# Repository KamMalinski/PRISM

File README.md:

# PRISM

**PCB Recognition and Intelligent Schematic Mapping**

PRISM reconstructs an editable KiCad schematic from aligned images of the top
and bottom sides of a PCB. It combines image processing, pad and trace
detection, OCR-assisted component recognition, connectivity analysis, manual
correction tools, and schematic optimization in one desktop application.

> PRISM is currently alpha software. Generated connectivity and component
> assignments must be reviewed before they are used for manufacturing,
> servicing, or safety-critical work.

## Features

- guided import of TOP and BOTTOM PCB images;
- automatic or manually sampled solder-mask and copper colors;
- board alignment, pad pairing, trace detection, and net reconstruction;
- OCR-assisted labels and component candidates;
- interactive correction editor for pads, traces, pairs, OCR, and components;
- text netlist and KiCad schematic export;
- optional KiCad CLI validation and schematic optimization;
- native desktop builds for Windows, macOS, and Linux.

## Requirements

- Python 3.11 or newer when running from source;
- Tk 8.6 or newer;
- Tesseract OCR for OCR features;
- KiCad with `kicad-cli` for round-trip validation and optimized previews.

PRISM searches `PATH` first and then conventional installation locations for
the current operating system. Tesseract can also be selected manually in the
interface.

On Debian or Ubuntu, install the native GUI and OpenCV runtime libraries before
running from source or building:

```bash
sudo apt-get install python3-venv python3-tk libgl1 libglib2.0-0
```

## Run From Source

Create and activate a virtual environment, then install the project:

```bash
python -m venv .venv
```

Windows PowerShell:

```powershell
.\.venv\Scripts\Activate.ps1
python -m pip install -r requirements.txt
prism
```

macOS and Linux:

```bash
source .venv/bin/activate
python -m pip install -r requirements.txt
prism
```

Windows users can alternatively run `.\run.ps1`.

## Build Native Packages

PyInstaller creates native applications and does not cross-compile. Run the
matching script on each target operating system:

```powershell
# Windows
.\scripts\build\build_windows.ps1
```

```bash
# macOS
bash scripts/build/build_macos.sh

# Linux
bash scripts/build/build_linux.sh
```

The scripts create an isolated `.venv-build` environment and use the shared
configuration in `scripts/build/package.py`.

| Platform | Output |
| --- | --- |
| Windows | `dist/PRISM/PRISM.exe` |
| macOS | `dist/PRISM.app` |
| Linux | `dist/PRISM/PRISM` |

Windows and Linux use PyInstaller's `onedir` layout. Distribute the complete
`dist/PRISM` directory, not only the executable. The macOS application is
unsigned; public releases should be code-signed and notarized by the release
owner.

## Basic Workflow

1. Select images of the top and bottom PCB sides.
2. Confirm automatic color detection or collect color samples manually.
3. Run the analysis.
4. Review detected geometry and connectivity in the correction editor.
5. Recalculate after corrections and inspect the generated netlist.
6. Open the result directory and validate the KiCad schematic.

Generated files are written under `~/PRISM/results` by default. Set the
`PRISM_OUTPUT_DIR` environment variable to use a different location. A local
`results/` directory is also excluded from version control.

## Dataset

[`Dataset/`](Dataset/README.md) contains twelve PCB examples with TOP/BOTTOM
images and reference KiCad projects. It is intended for repeatable development
and evaluation, not as a formal train/test split.

## Project Structure

```text
.
|-- Dataset/                         Test images and reference KiCad projects
|-- scripts/build/                   Native build entry points and shared build logic
|-- src/schematic_generator/
|   |-- assets/                      Application and executable icons
|   |-- correction_editor/           Manual reconstruction editor
|   |-- detection/                   Pad, trace, plane, and pair detection
|   |-- diagnostics/                 Diagnostic reports
|   |-- geometry/                    Alignment and rectification
|   |-- gui/                         Main desktop workflow
|   |-- kicad/                       KiCad serialization and routing
|   |-- netlist/                     Connectivity and component inference
|   |-- schematic/                   Validation and optimization
|   |-- platform_support.py          Operating-system integration
|   `-- __main__.py                  Application entry point
|-- pyproject.toml                  Package metadata and runtime dependencies
|-- requirements-build.txt          Build-only dependencies
`-- requirements.txt                Editable development installation
```

## Automated Builds

The GitHub Actions workflow in `.github/workflows/build.yml` runs smoke tests
and creates Windows, macOS, and Linux artifacts using the same scripts as local
builds.

## Contributing

Keep platform-independent behavior in the application modules. Operating-system
differences belong in `platform_support.py`, while packaging differences belong
in `scripts/build/package.py`. New detection or reconstruction behavior should
be checked against multiple samples from `Dataset/`.

## License

No project license has been selected yet. Add a `LICENSE` file before presenting
PRISM as open-source software or accepting external contributions.

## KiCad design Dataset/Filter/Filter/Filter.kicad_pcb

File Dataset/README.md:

# PCB Test Dataset

This directory contains a curated test dataset of small PCB examples used for
evaluating PCB image analysis and schematic reconstruction workflows.

Each sample contains:

- two raster images of the PCB, one for the top side and one for the bottom
  side;
- a KiCad project directory with the reference PCB and schematic files.

## Directory Structure

The dataset is organized by sample name:

```text
Dataset/
  Cascade/
    TOP.png
    BOTTOM.png
    Cascade/
      Cascade.kicad_pcb
      Cascade.kicad_sch
      Cascade.kicad_pro
      Cascade.kicad_prl
  Connector/
    TOP.png
    BOTTOM.png
    Connector/
      Connector.kicad_pcb
      Connector.kicad_sch
      Connector.kicad_pro
      Connector.kicad_prl
  ...
```

## Samples

| Sample | Purpose / PCB feature represented | Top image | Bottom image | KiCad project folder |
| --- | --- | --- | --- | --- |
| `Cascade` | Cascaded circuit blocks and multi-stage connectivity | `TOP.png` | `BOTTOM.png` | `Cascade/` |
| `Connector` | Connector-style topology and external pin grouping | `TOP.png` | `BOTTOM.png` | `Connector/` |
| `Crossover` | Crossing or overlapping routing patterns between nets | `TOP.png` | `BOTTOM.png` | `Crossover/` |
| `Divider` | Simple divider-like circuit topology | `TOP.png` | `BOTTOM.png` | `Divider/` |
| `Elements` | Board with a larger number of components/elements | `TOP.png` | `BOTTOM.png` | `Elements/` |
| `Filter` | Filter-like circuit topology | `TOP.png` | `BOTTOM.png` | `Filter/` |
| `Floating` | Floating or weakly connected structures | `TOP.png` | `BOTTOM.png` | `Floating/` |
| `Groundplane` | Board containing a large copper groundplane/fill area | `TOP.png` | `BOTTOM.png` | `Groundplane/` |
| `Meander` | Meandered routing geometry | `TOP.png` | `BOTTOM.png` | `Meander/` |
| `Round` | Rounded or curved routing geometry | `TOP.png` | `BOTTOM.png` | `Round/` |
| `Simple` | Simple baseline board | `TOP.png` | `BOTTOM.png` | `Simple/` |
| `Transistors` | Board containing transistor-based circuitry | `TOP.png` | `BOTTOM.png` | `Transistors/` |

## File Formats

The raster images are PNG files. They should be interpreted as pixel images of
the PCB sides:

- `TOP.png` - top side image;
- `BOTTOM.png` - bottom side image.

The KiCad project directories contain:

- `*.kicad_pcb` - reference PCB layout;
- `*.kicad_sch` - reference schematic;
- `*.kicad_pro` - KiCad project metadata;
- `*.kicad_prl` - KiCad project local/session settings.

The KiCad files are intended as reference design files for validating generated
schematics, connectivity, component placement, and PCB reconstruction results.

## How to Interpret the Data

The PNG images are the primary inputs for image-processing and reconstruction
algorithms. The corresponding KiCad files are the reference data for the same
sample.

When using the dataset:

1. Treat each top-level directory as one independent PCB test case.
2. Load the top and bottom PNG images as the two observed PCB sides.
3. Use the KiCad files in the nested project directory as reference design
   data.
4. Compare generated outputs against the reference schematic or PCB project,
   depending on the evaluated task.

The dataset does not define a train/test split. If a split is needed, define it
explicitly in the experiment protocol.

## Expected Use

This dataset is suitable for:

- testing PCB side alignment;
- detecting pads, traces, holes, copper pours, and component-like structures;
- reconstructing netlists from PCB images;
- generating or validating KiCad schematic files;
- comparing algorithm behavior on boards with different routing patterns.

## Notes

- Raster image units are pixels.
- KiCad coordinate data should be interpreted according to KiCad file format
  conventions, typically in millimeters for design coordinates.
- The dataset contains PCB design examples and does not contain personal or
  human-subject data.

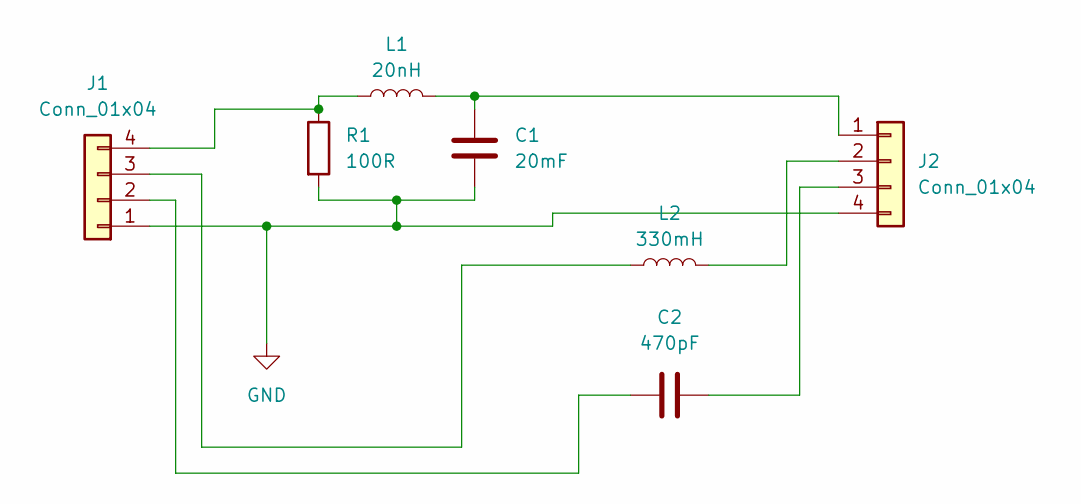
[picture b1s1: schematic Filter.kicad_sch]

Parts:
C1: 20mF; CP_Radial_Tantal_D8.0mm_P5.00mm
C2: 470pF; C_Rect_L9.0mm_W4.9mm_P7.50mm_MKT
J1: Conn_01x04; SolderWire-0.5sqmm_1x04_P4.8mm_D0.9mm_OD2.3mm
J2: Conn_01x04; PinHeader_1x04_P2.54mm_Horizontal
L1: 20nH; L_Axial_L20.0mm_D8.0mm_P7.62mm_Vertical
L2: 330mH; L_Axial_L29.9mm_D14.0mm_P38.00mm_Horizontal_Vishay_IHA-105
R1: 100R; R_Axial_Power_L20.0mm_W6.4mm_P25.40mm

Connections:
GND: C1.2, J1.1, J2.4, R1.2
unnamed: C2.1, J1.2
unnamed: J1.3, L2.1
unnamed: J1.4, L1.1, R1.1
unnamed: C1.1, J2.1, L1.2
unnamed: J2.2, L2.2
unnamed: C2.2, J2.3

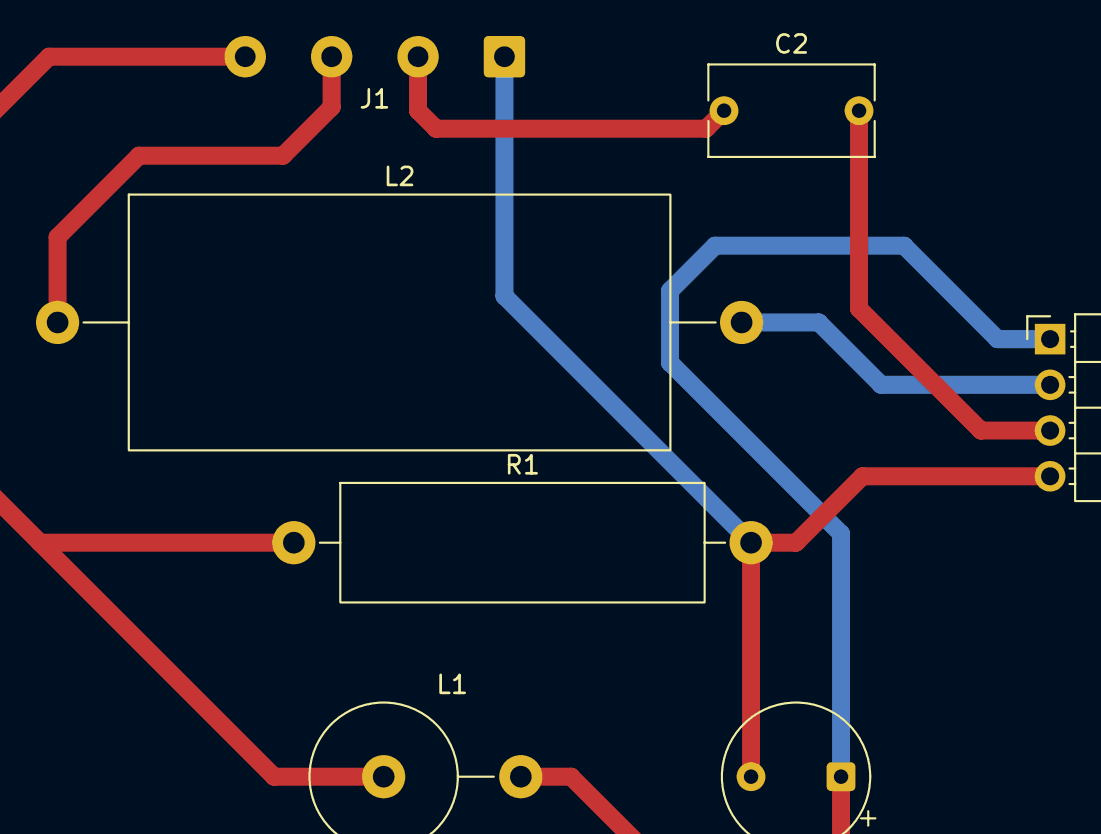
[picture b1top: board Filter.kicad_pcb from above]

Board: 2 copper layers, 7 parts (0 on the bottom side), 7 nets.

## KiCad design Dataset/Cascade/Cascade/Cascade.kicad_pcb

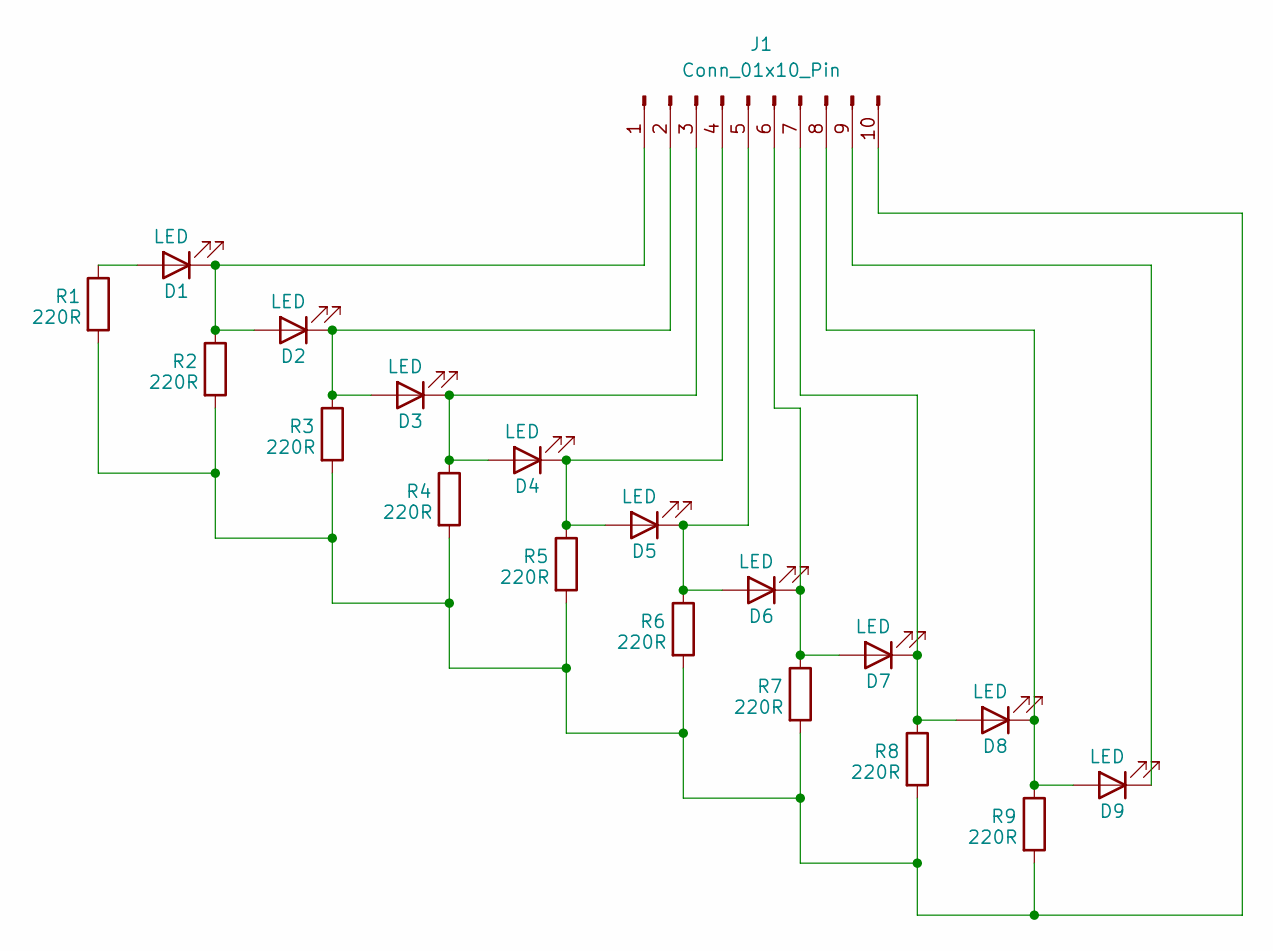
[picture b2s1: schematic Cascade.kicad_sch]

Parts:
D1, D2, D3, D4, D5, D6, D7, D8, D9: LED; LED_D3.0mm
J1: Conn_01x10_Pin; PhoenixContact_MSTBA_2,5_10-G_1x10_P5.00mm_Horizontal
R1, R2, R3, R4, R5, R6, R7, R8, R9: 220R; R_Axial_DIN0614_L14.3mm_D5.7mm_P20.32mm_Horizontal

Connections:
unnamed: D1.2 (A), R1.1
unnamed: D1.1 (K), D2.2 (A), J1.1, R2.1
unnamed: D2.1 (K), D3.2 (A), J1.2, R3.1
unnamed: D3.1 (K), D4.2 (A), J1.3, R4.1
unnamed: D4.1 (K), D5.2 (A), J1.4, R5.1
unnamed: D5.1 (K), D6.2 (A), J1.5, R6.1
unnamed: D6.1 (K), D7.2 (A), J1.6, R7.1
unnamed: D7.1 (K), D8.2 (A), J1.7, R8.1
unnamed: D8.1 (K), D9.2 (A), J1.8, R9.1
unnamed: D9.1 (K), J1.9
unnamed: J1.10, R1.2, R2.2, R3.2, R4.2, R5.2, R6.2, R7.2, R8.2, R9.2

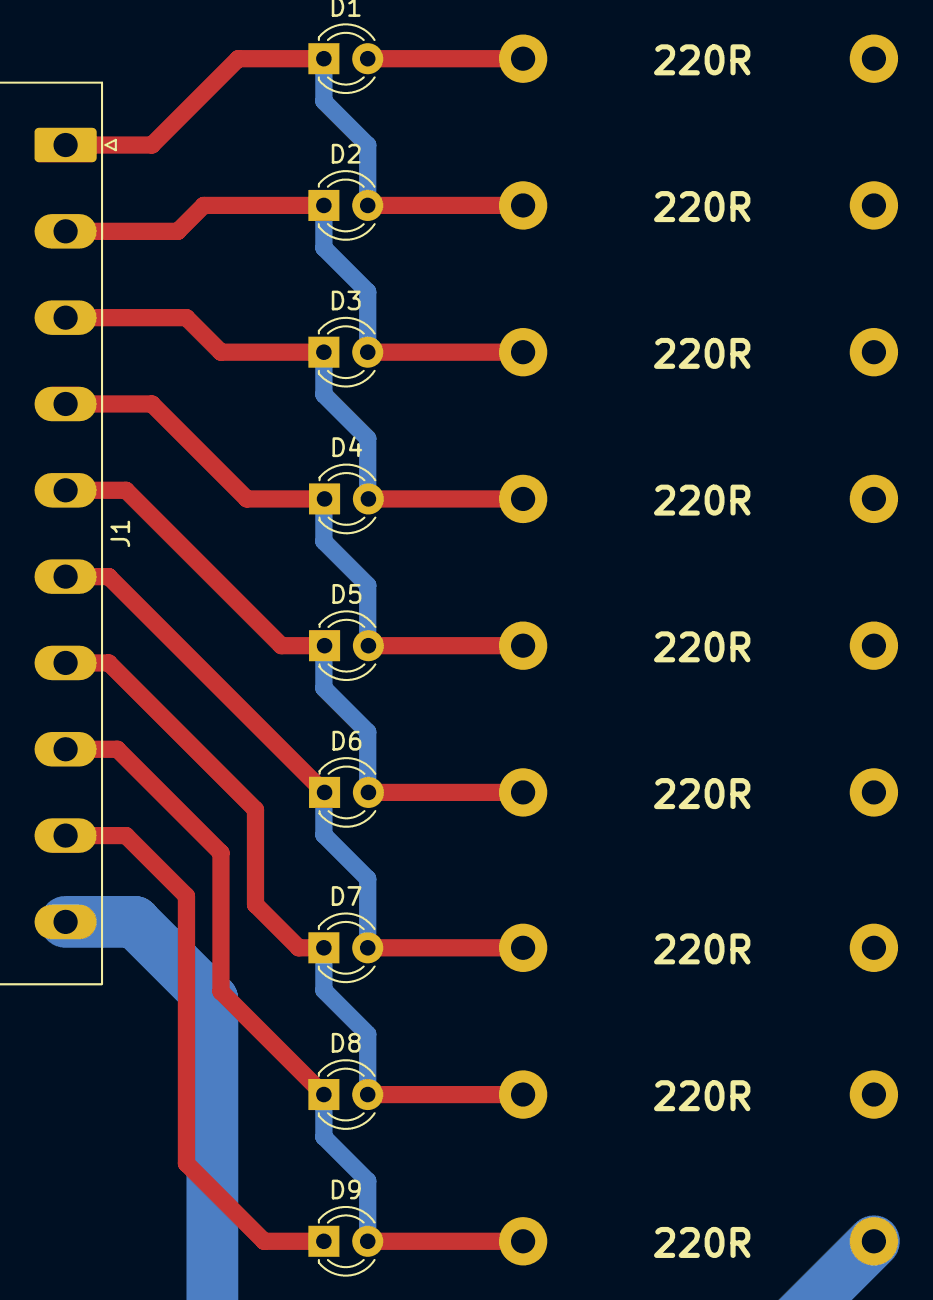
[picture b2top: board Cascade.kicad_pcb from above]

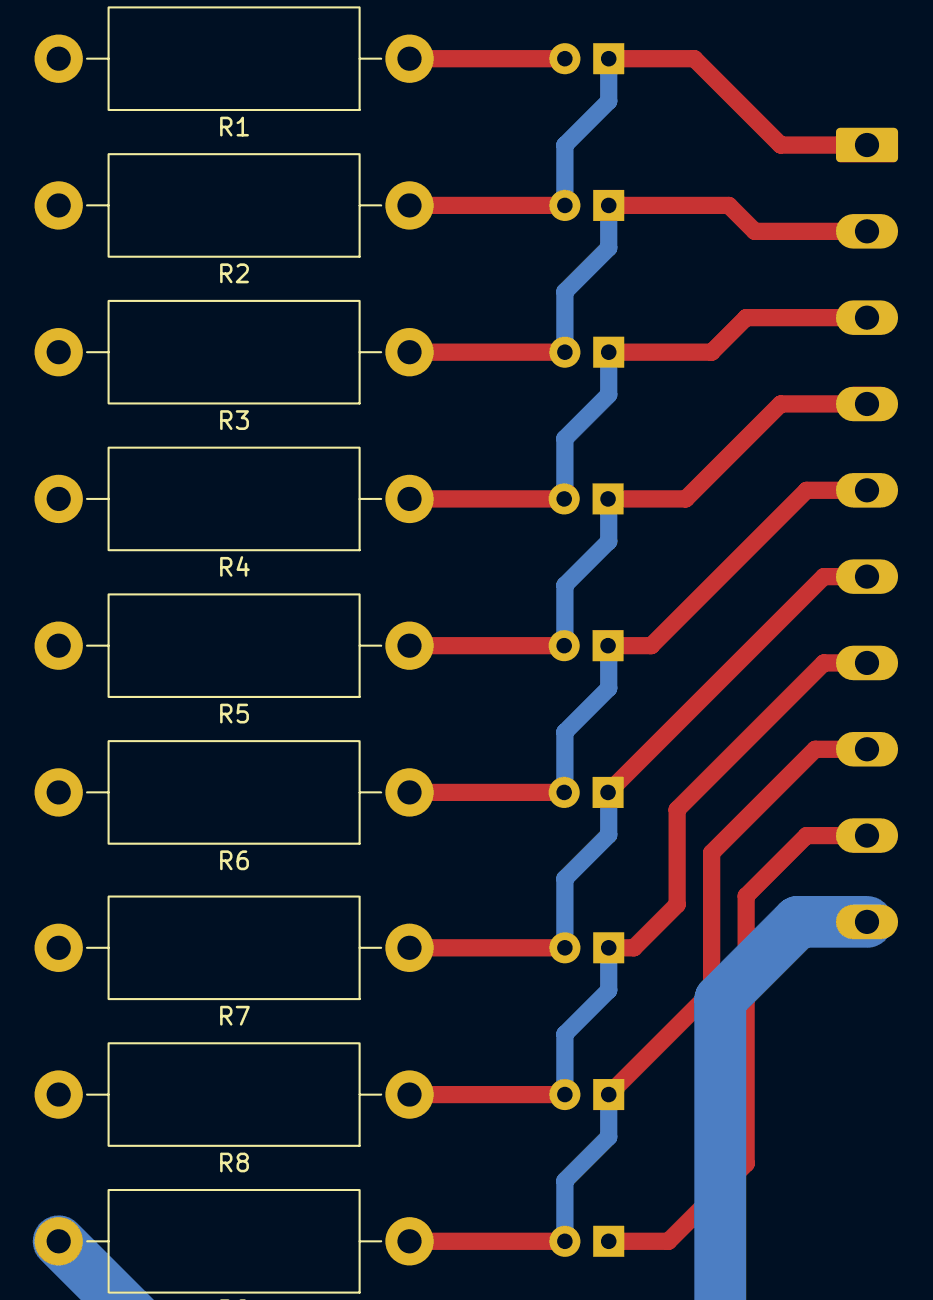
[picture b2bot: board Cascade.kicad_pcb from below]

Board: 2 copper layers, 19 parts (9 on the bottom side), 11 nets.

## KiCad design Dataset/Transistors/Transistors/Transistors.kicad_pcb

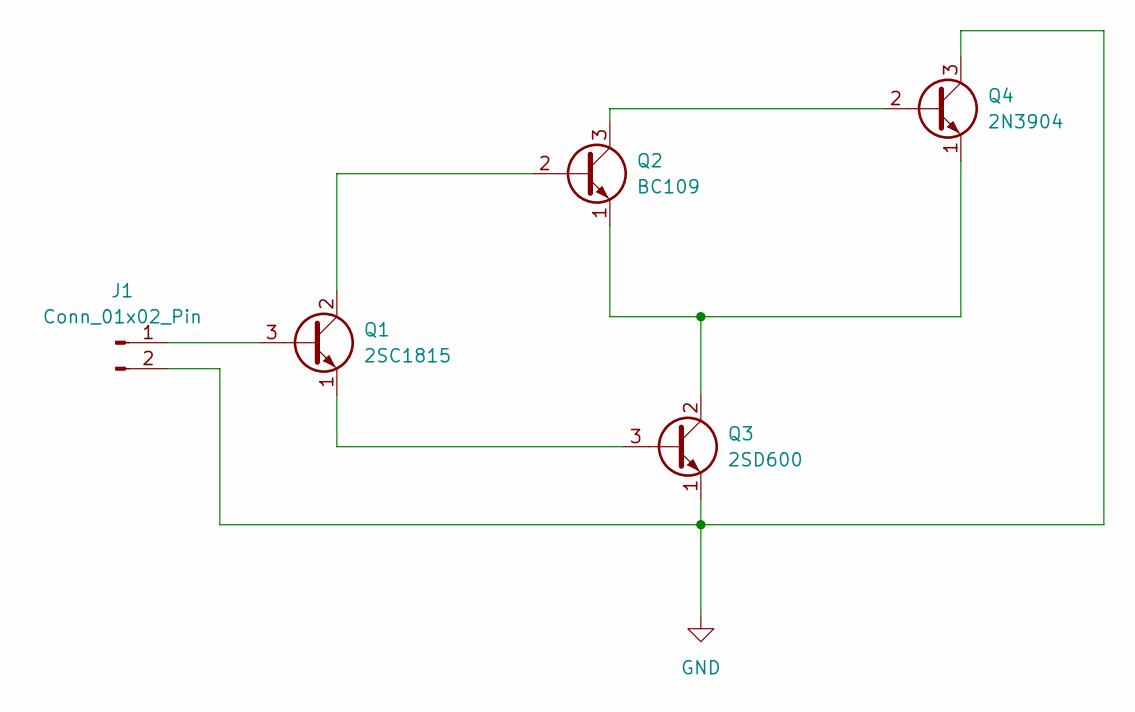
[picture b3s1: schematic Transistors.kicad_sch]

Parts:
J1: Conn_01x02_Pin; AMASS_XT60-M_1x02_P7.20mm_Vertical
Q1: 2SC1815; TO-92_Inline
Q2: BC109; TO-18-3
Q3: 2SD600; TO-126-3_Vertical
Q4: 2N3904; TO-92_Wide

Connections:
GND: J1.2, Q3.1 (E), Q4.3 (C)
unnamed: J1.1, Q1.3 (B)
unnamed: Q1.2 (C), Q2.2 (B)
unnamed: Q1.1 (E), Q3.3 (B)
unnamed: Q2.3 (C), Q4.2 (B)
unnamed: Q2.1 (E), Q3.2 (C), Q4.1 (E)

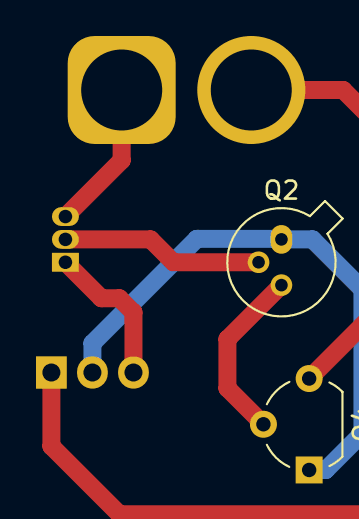
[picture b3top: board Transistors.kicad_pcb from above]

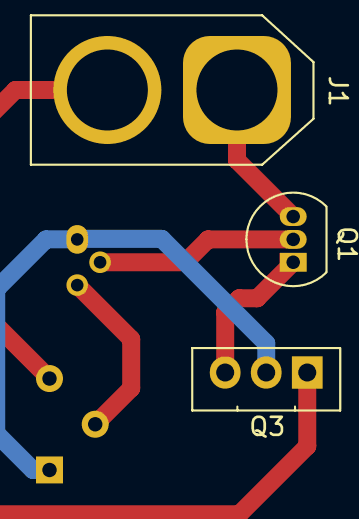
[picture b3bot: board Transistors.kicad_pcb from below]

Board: 2 copper layers, 5 parts (3 on the bottom side), 6 nets.

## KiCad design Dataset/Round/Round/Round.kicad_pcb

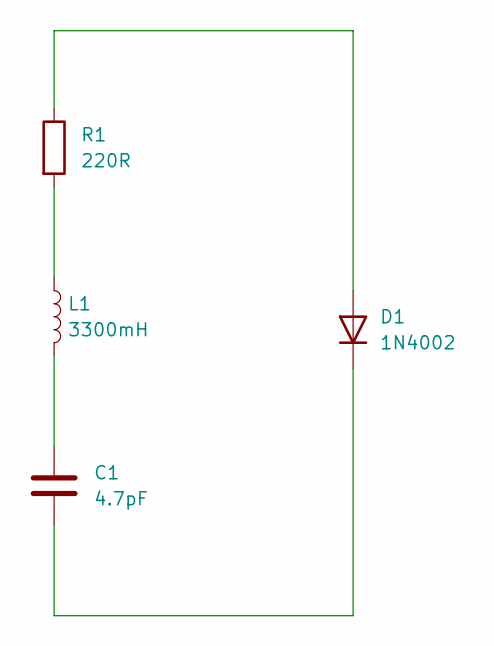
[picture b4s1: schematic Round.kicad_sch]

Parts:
C1: 4.7pF; C_Axial_L12.0mm_D6.5mm_P15.00mm_Horizontal
D1: 1N4002; D_DO-41_SOD81_P10.16mm_Horizontal
L1: 3300mH; L_Axial_L16.0mm_D9.5mm_P20.32mm_Horizontal_Vishay_IM-10-37
R1: 220R; R_Axial_DIN0614_L14.3mm_D5.7mm_P7.62mm_Vertical

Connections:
unnamed: C1.1, L1.2
unnamed: D1.2 (A), R1.1
unnamed: C1.2, D1.1 (K)
unnamed: L1.1, R1.2

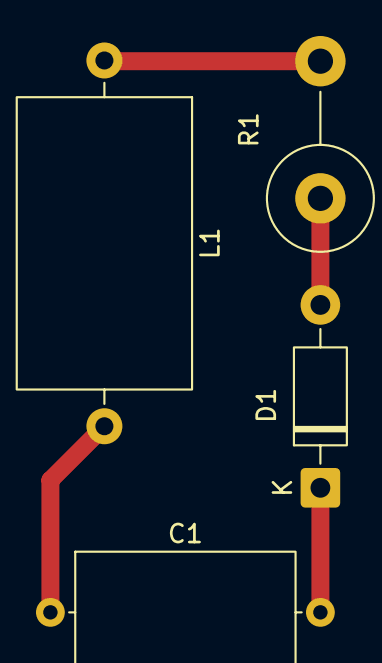
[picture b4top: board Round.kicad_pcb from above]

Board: 2 copper layers, 4 parts (0 on the bottom side), 4 nets.

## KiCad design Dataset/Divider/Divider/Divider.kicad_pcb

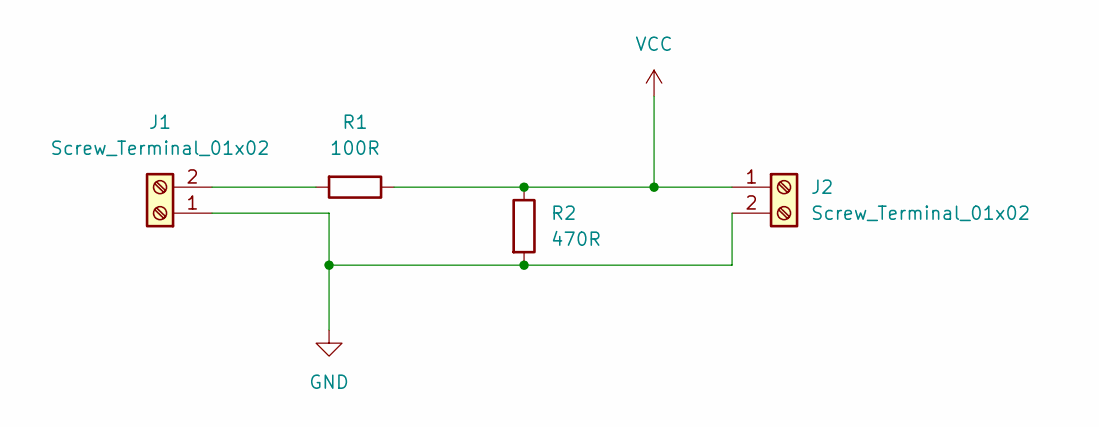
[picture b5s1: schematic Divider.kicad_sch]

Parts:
J1, J2: Screw_Terminal_01x02; Wuerth_691311400102_P7.62mm
R1: 100R; R_Axial_DIN0516_L15.5mm_D5.0mm_P25.40mm_Horizontal
R2: 470R; R_Axial_DIN0516_L15.5mm_D5.0mm_P25.40mm_Horizontal

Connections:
GND: J1.1, J2.2, R2.2
unnamed: J1.2, R1.2
VCC: J2.1, R1.1, R2.1

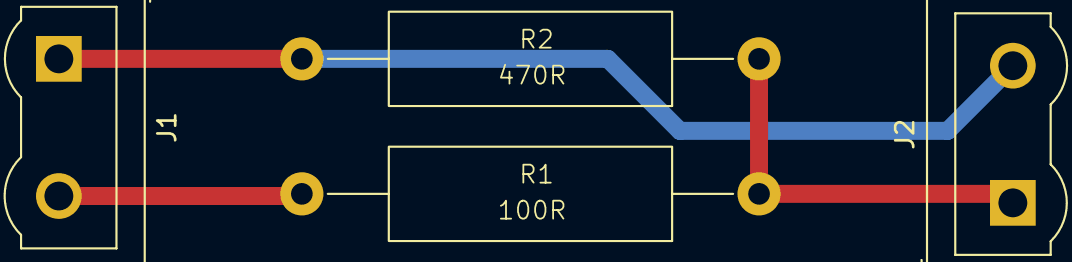
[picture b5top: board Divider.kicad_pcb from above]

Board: 2 copper layers, 4 parts (0 on the bottom side), 3 nets.

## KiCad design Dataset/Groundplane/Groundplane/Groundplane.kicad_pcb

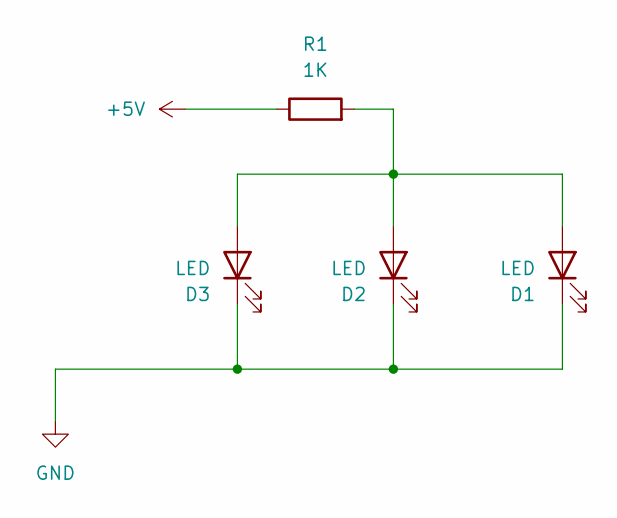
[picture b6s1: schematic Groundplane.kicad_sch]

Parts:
D1, D2, D3: LED; LED_D10.0mm
R1: 1K; R_Axial_DIN0918_L18.0mm_D9.0mm_P25.40mm_Horizontal

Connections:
+5V: R1.1
GND: D1.1 (K), D2.1 (K), D3.1 (K)
unnamed: D1.2 (A), D2.2 (A), D3.2 (A), R1.2

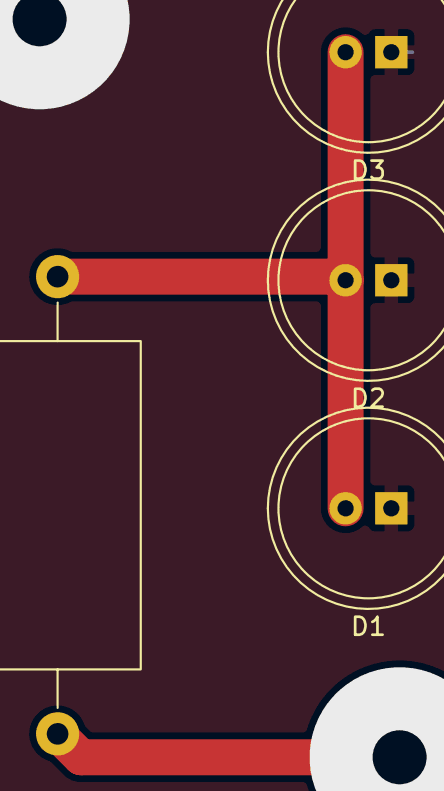
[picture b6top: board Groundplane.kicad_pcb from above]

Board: 2 copper layers, 4 parts (0 on the bottom side), 2 nets.

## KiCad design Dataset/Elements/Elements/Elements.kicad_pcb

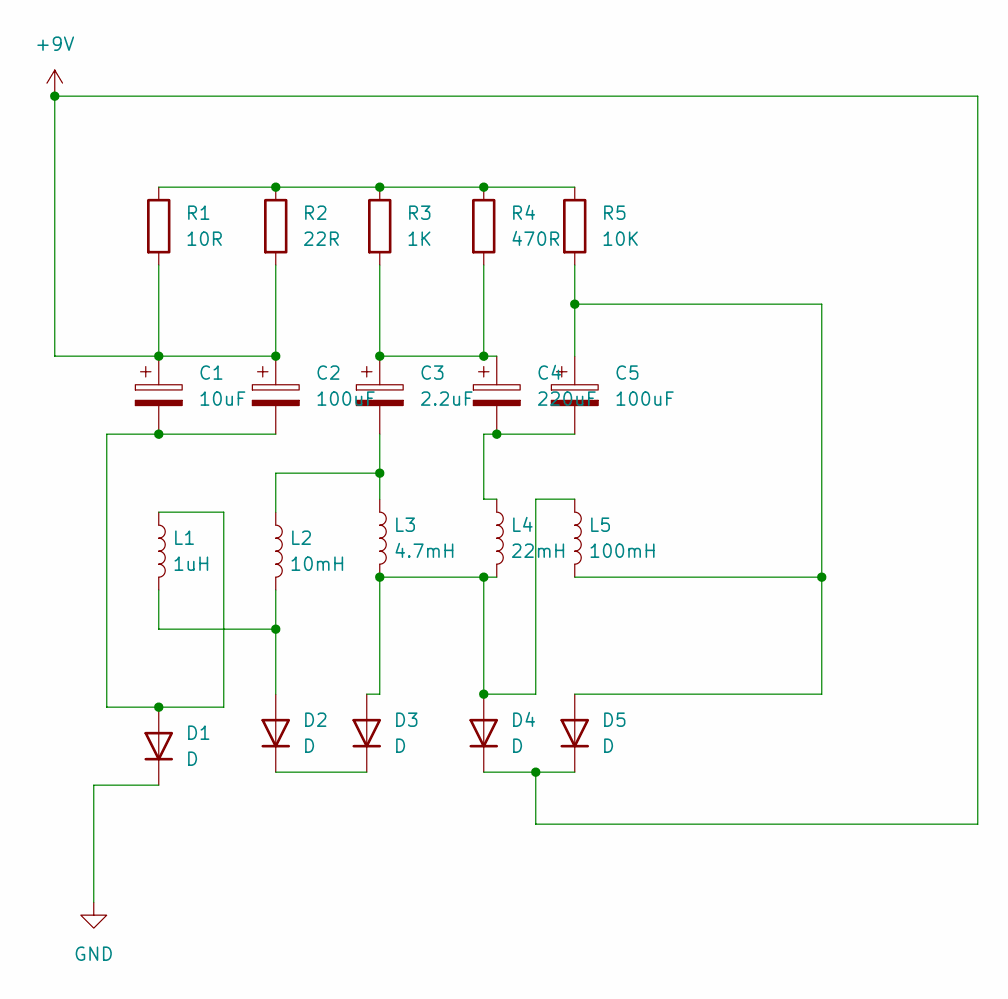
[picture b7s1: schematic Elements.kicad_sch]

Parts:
C1: 10uF; C_Radial_D4.0mm_H5.0mm_P1.50mm
C2: 100uF; C_Radial_D10.0mm_H16.0mm_P5.00mm
C3: 2.2uF; CP_Axial_L80.0mm_D35.0mm_P85.00mm_Horizontal
C4: 220uF; CP_Radial_D7.5mm_P2.50mm
C5: 100uF; CP_Radial_D14.0mm_P7.50mm
D1: D; D_5W_P10.16mm_Horizontal
D2: D; D_A-405_P10.16mm_Horizontal
D3: D; D_DO-15_P10.16mm_Horizontal
D4: D; D_DO-35_SOD27_P3.81mm_Vertical_AnodeUp
D5: D; D_DO-201AE_P15.24mm_Horizontal
L1: 1uH; L_Radial_D7.5mm_P5.00mm_Fastron_07P
L2: 10mH; L_Axial_L7.0mm_D3.3mm_P12.70mm_Horizontal_Fastron_MICC
L3: 4.7mH; L_Axial_L12.8mm_D5.8mm_P20.32mm_Horizontal_Fastron_HBCC
L4: 22mH; L_Axial_L24.0mm_D7.1mm_P5.08mm_Vertical_Vishay_IM-10-28
L5: 100mH; L_Axial_L14.0mm_D4.5mm_P5.08mm_Vertical_Fastron_LACC
R1: 10R; R_Axial_DIN0516_L15.5mm_D5.0mm_P20.32mm_Horizontal
R2: 22R; R_Axial_DIN0614_L14.3mm_D5.7mm_P15.24mm_Horizontal
R3: 1K; R_Axial_DIN0617_L17.0mm_D6.0mm_P25.40mm_Horizontal
R4: 470R; R_Axial_DIN0918_L18.0mm_D9.0mm_P25.40mm_Horizontal
R5: 10K; R_Axial_Power_L20.0mm_W6.4mm_P5.08mm_Vertical

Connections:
+9V: C1.1, C2.1, D4.1 (K), D5.1 (K), R1.2, R2.2
GND: D1.1 (K)
unnamed: C3.1, C4.1, R3.2, R4.2
unnamed: C3.2, L2.1, L3.1
unnamed: C4.2, C5.2, L4.1
unnamed: C1.2, C2.2, D1.2 (A), L1.1
unnamed: D2.2 (A), L1.2, L2.2
unnamed: D2.1 (K), D3.1 (K)
unnamed: D3.2 (A), D4.2 (A), L3.2, L4.2, L5.1
unnamed: C5.1, D5.2 (A), L5.2, R5.2
unnamed: R1.1, R2.1, R3.1, R4.1, R5.1

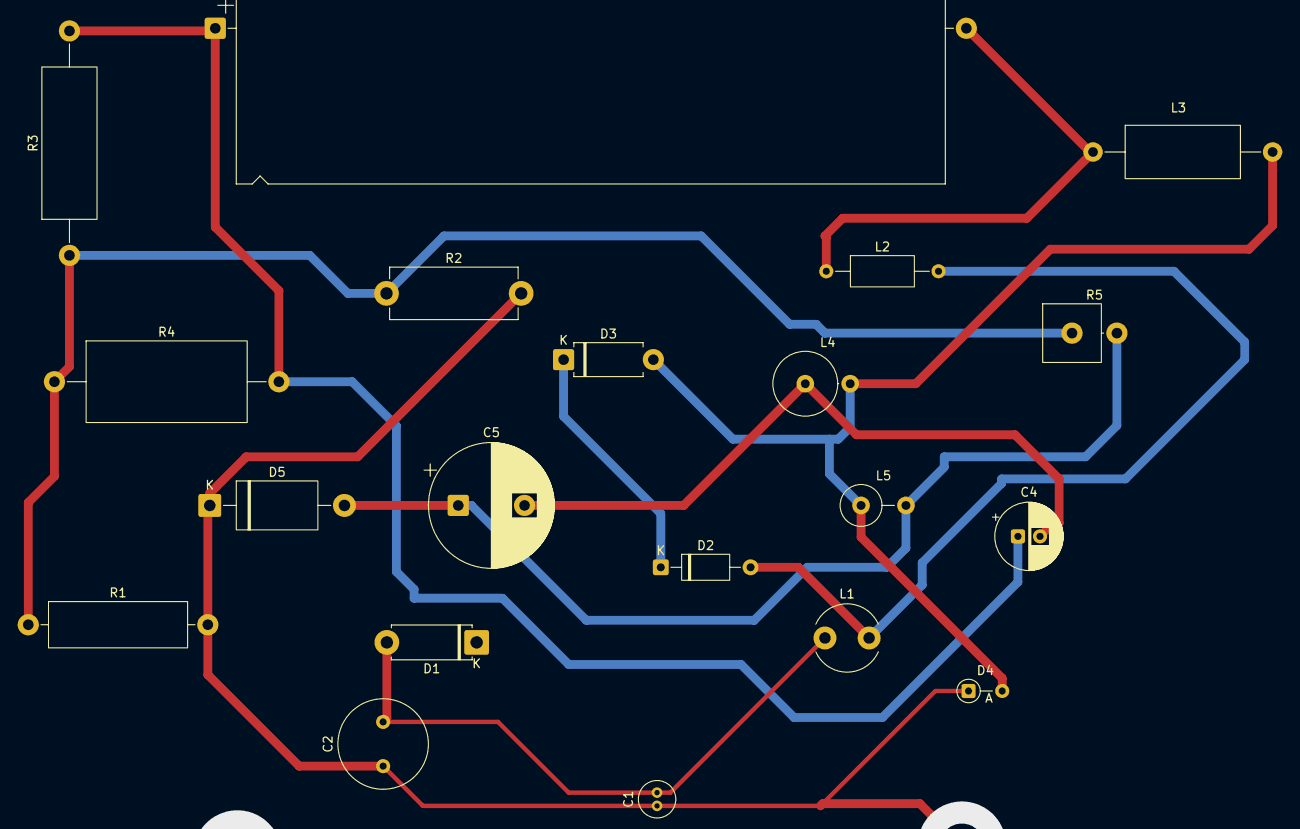
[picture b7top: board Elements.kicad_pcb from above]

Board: 2 copper layers, 20 parts (0 on the bottom side), 10 nets.

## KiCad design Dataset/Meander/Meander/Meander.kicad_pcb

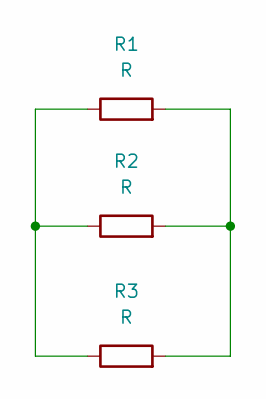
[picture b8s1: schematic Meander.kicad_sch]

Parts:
R1, R2, R3: R; R_Axial_DIN0309_L9.0mm_D3.2mm_P12.70mm_Horizontal

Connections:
unnamed: R1.1, R2.1, R3.1
unnamed: R1.2, R2.2, R3.2

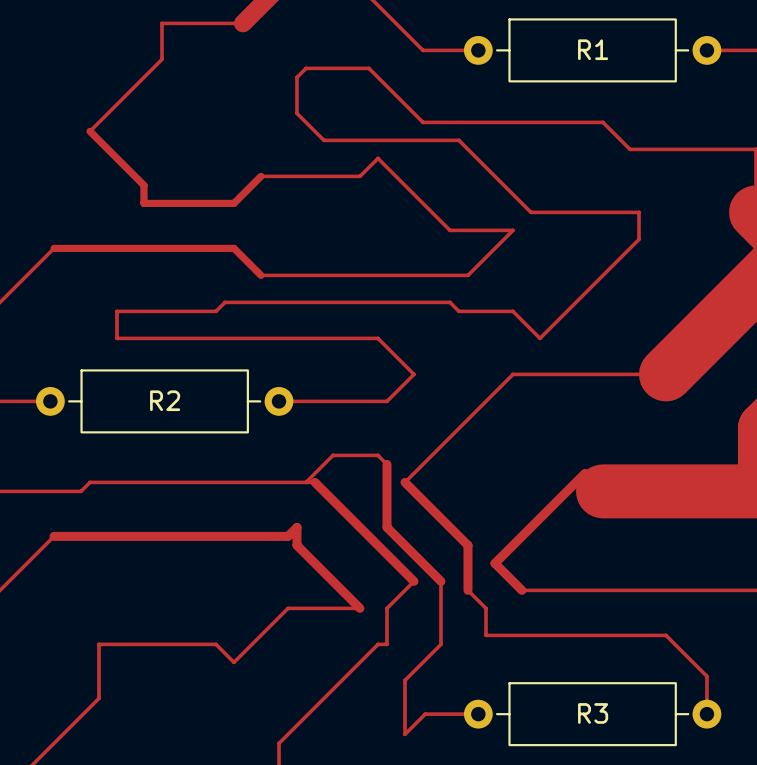
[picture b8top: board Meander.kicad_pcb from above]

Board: 2 copper layers, 3 parts (0 on the bottom side), 2 nets.
